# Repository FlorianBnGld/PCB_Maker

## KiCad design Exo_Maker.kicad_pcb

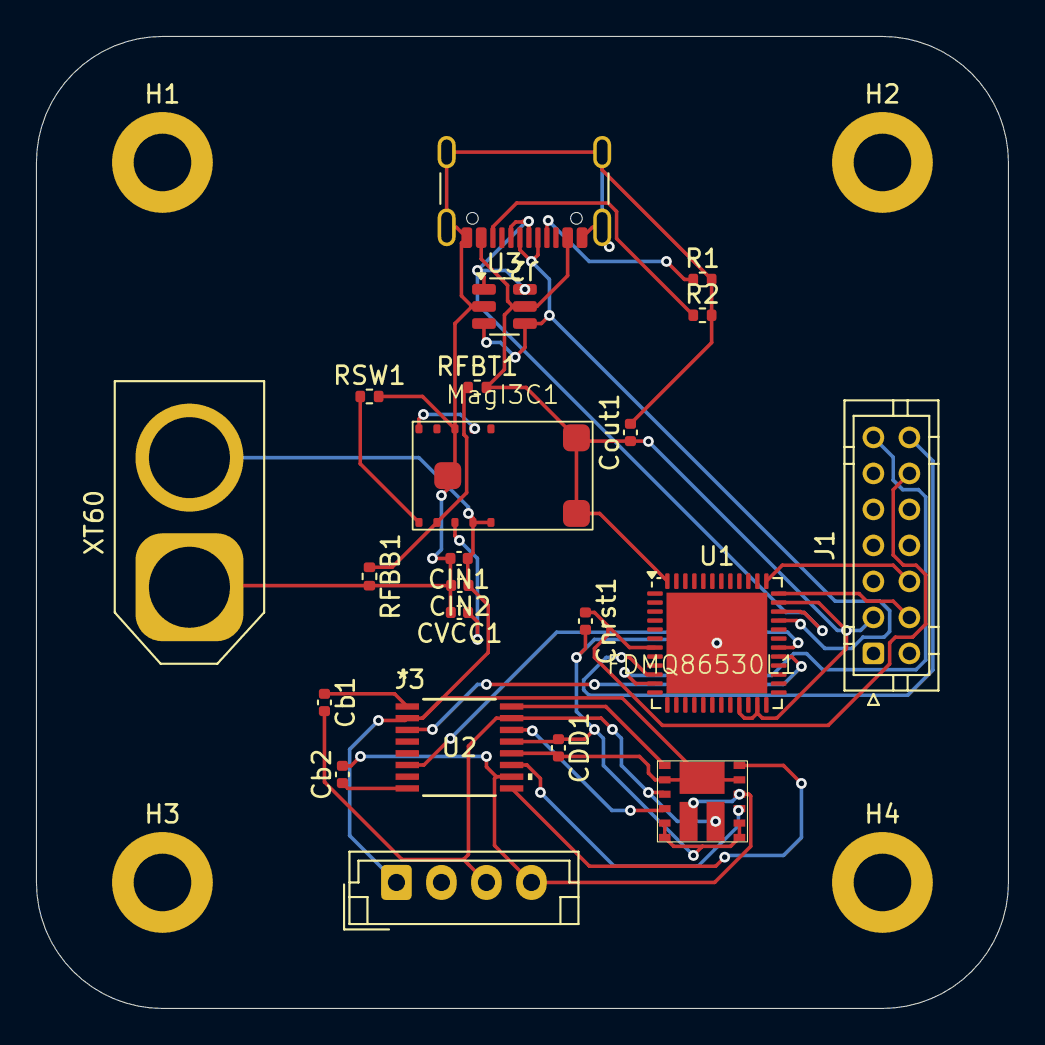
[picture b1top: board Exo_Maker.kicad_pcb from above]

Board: 4 copper layers, 54.0 x 54.0 mm, 26 parts (0 on the bottom side), 26 nets.

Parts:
CDD1: 2u; C_0402_1005Metric
CIN1, CIN2: 4,7u; C_0402_1005Metric
CVCC1: 1u; C_0402_1005Metric
Cb1, Cb2: 0,5u; C_0402_1005Metric
Cnrst1: 0,1u; C_0402_1005Metric
Cout1: 47u; C_0402_1005Metric
FDMQ86530L1: MOSFET_FDMQ86530L
H1, H2, H3, H4: MountingHole_Pad; MountingHole_3.2mm_M3_DIN965_Pad
J1: Conn_02x07_Odd_Even; JST_PHD_B14B-PHDSS_2x07_P2.00mm_Vertical
J2: USB_C_Receptacle_USB2.0_16P; USB_C_Receptacle_GCT_USB4105-xx-A_16P_TopMnt_Horizontal
J3: Conn_01x04; JST_EH_B4B-EH-A_1x04_P2.50mm_Vertical
MagI3C1: 171013801
R1, R2: 5,1k; R_0402_1005Metric
RFBB1: 137k; R_0402_1005Metric
RFBT1: 402k; R_0402_1005Metric
RSW1: 5,6k; R_0402_1005Metric
U1: STM32G431CBUx; QFN-48-1EP_7x7mm_P0.5mm_EP5.6x5.6mm
U2: MIC4606-2YTS-TR; TSSOP16_TS_MCH_MIS
U3: USBLC6-2SC6; SOT-23-6
XT60: Connector; AMASS_XT60-F_1x02_P7.20mm_Vertical

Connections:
AHO: FDMQ86530L1.12 (G4), U2.9 (AHO)
AHS: Cb2.2, FDMQ86530L1.10 (D3/S4), FDMQ86530L1.14 (D3/S4), J3.4, U2.10 (AHS)
ALO: FDMQ86530L1.9 (G3), U2.11 (ALO)
APWM: U1.30 (PA8), U2.6 (APWM)
BHO: FDMQ86530L1.1 (G1), U2.16 (BHO)
BHS: Cb1.2, FDMQ86530L1.3 (S1/D2), FDMQ86530L1.15 (S1/D2), J3.3, U2.15 (BHS)
BLO: FDMQ86530L1.4 (G2), U2.14 (BLO)
BPWM: U1.29 (PC6), U2.3 (BPWM)
D+: J2.A6 (D+), J2.B6 (D+), U1.34 (PA12), U3.1 (I/O1), U3.6 (I/O1)
D-: J2.A7 (D-), J2.B7 (D-), U1.33 (PA11), U3.3 (I/O2), U3.4 (I/O2)
GND: CDD1.1, CIN1.2, CIN2.2, CVCC1.2, Cnrst1.2, Cout1.2, FDMQ86530L1.5 (S2), FDMQ86530L1.6 (S2), FDMQ86530L1.7 (S3), FDMQ86530L1.8 (S3), H1.1, H2.1, H3.1, H4.1, J1.5, J1.7, J1.11, J2.A1 (GND), J2.A12 (GND), J2.B1 (GND), J2.B12 (GND), J2.S1 (SHIELD), J3.2, MagI3C1.10 (AGND), MagI3C1.13 (PGND), R1.2, R2.2, RFBB1.2, RSW1.2, U1.49 (VSS), U2.13 (VSS), U3.2 (GND), XT60.1 (+)
NRST: Cnrst1.1, J1.12, U1.7 (PG10)
unnamed: J2.A5 (CC1), R1.1
unnamed: J2.B5 (CC2), R2.1
unnamed: MagI3C1.9 (VIN), MagI3C1.12 (EN)
unnamed: MagI3C1.2 (FB), RFBB1.1, RFBT1.1
unnamed: MagI3C1.1 (FSW), RSW1.1
unnamed: CVCC1.1, MagI3C1.3 (VCC)
unnamed: Cb2.1, U2.8 (AHB)
unnamed: Cb1.1, U2.1 (BHB)
SWDCK: J1.6, U1.37 (PA14)
SWDIO: J1.4, U1.36 (PA13)
USART2_RX: J1.13, U1.11 (PA3)
USART2_TX: J1.14, U1.10 (PA2)
VALIM: CDD1.2, CIN1.1, CIN2.1, FDMQ86530L1.2 (D1/D4), FDMQ86530L1.11 (D1/D4), FDMQ86530L1.13 (D1/D4), J3.1, MagI3C1.4 (VIN), MagI3C1.5 (VIN), U2.2 (EN), U2.12 (VDD), XT60.2 (-)
VOUT: Cout1.1, J1.3, J2.A4 (VBUS), J2.A9 (VBUS), J2.B4 (VBUS), J2.B9 (VBUS), MagI3C1.6 (VOUT), MagI3C1.7 (VOUT), RFBT1.2, U1.21 (VDDA), U1.23 (VDD), U1.35 (VDD), U1.48 (VDD), U3.5 (VBUS)

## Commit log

2025-02-03 Create PCB
